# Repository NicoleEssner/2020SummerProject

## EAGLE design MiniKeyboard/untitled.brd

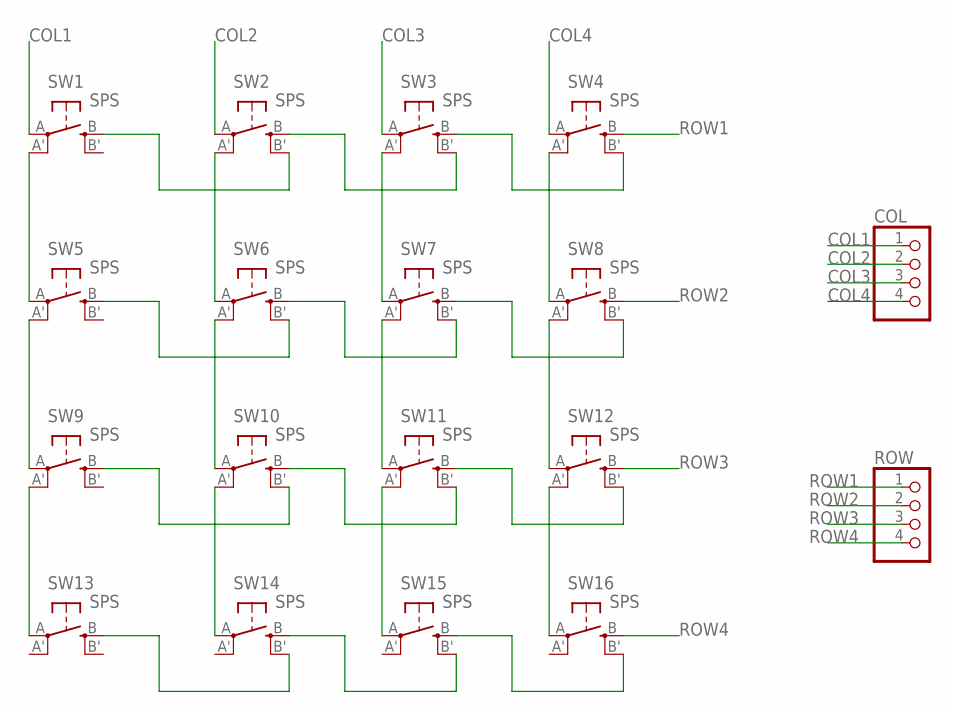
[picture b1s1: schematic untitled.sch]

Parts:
COL: PINHD-1X4; 1X04
ROW: PINHD-1X4; 1X04
SW1, SW2, SW3, SW4, SW5, SW6, SW7, SW8, SW9, SW10, SW11, SW12, SW13, SW14, SW15, SW16: SPS; EVQ-Q2

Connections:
COL1: COL.1, SW1.A
COL2: COL.2, SW2.A
COL3: COL.3, SW3.A
COL4: COL.4, SW4.A
unnamed: SW1.A' (P1), SW5.A
unnamed: SW5.A' (P1), SW9.A
unnamed: SW9.A' (P1), SW13.A
unnamed: SW2.A' (P1), SW6.A
unnamed: SW6.A' (P1), SW10.A
unnamed: SW10.A' (P1), SW14.A
unnamed: SW3.A' (P1), SW7.A
unnamed: SW7.A' (P1), SW11.A
unnamed: SW11.A' (P1), SW15.A
unnamed: SW4.A' (P1), SW8.A
unnamed: SW8.A' (P1), SW12.A
unnamed: SW12.A' (P1), SW16.A
unnamed: SW1.B (S), SW2.B' (S1)
unnamed: SW2.B (S), SW3.B' (S1)
unnamed: SW3.B (S), SW4.B' (S1)
unnamed: SW5.B (S), SW6.B' (S1)
unnamed: SW6.B (S), SW7.B' (S1)
unnamed: SW7.B (S), SW8.B' (S1)
unnamed: SW9.B (S), SW10.B' (S1)
unnamed: SW10.B (S), SW11.B' (S1)
unnamed: SW11.B (S), SW12.B' (S1)
unnamed: SW13.B (S), SW14.B' (S1)
unnamed: SW14.B (S), SW15.B' (S1)
unnamed: SW15.B (S), SW16.B' (S1)
ROW1: ROW.1, SW4.B (S)
ROW2: ROW.2, SW8.B (S)
ROW3: ROW.3, SW12.B (S)
ROW4: ROW.4, SW16.B (S)

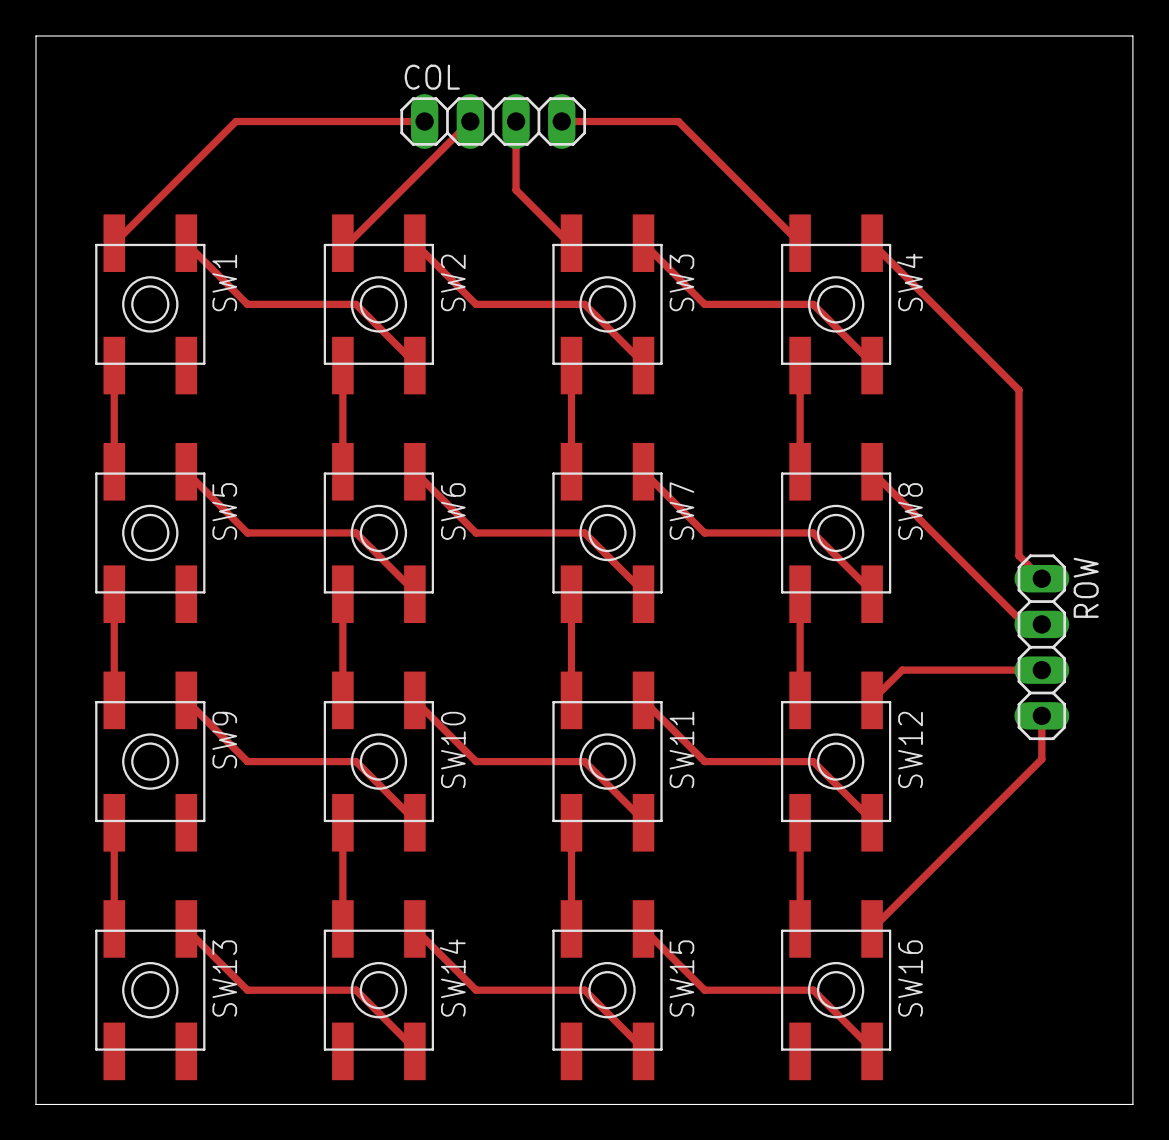
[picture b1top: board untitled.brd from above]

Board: 2 copper layers, 60.9 x 59.4 mm, 18 parts (0 on the bottom side), 32 nets.

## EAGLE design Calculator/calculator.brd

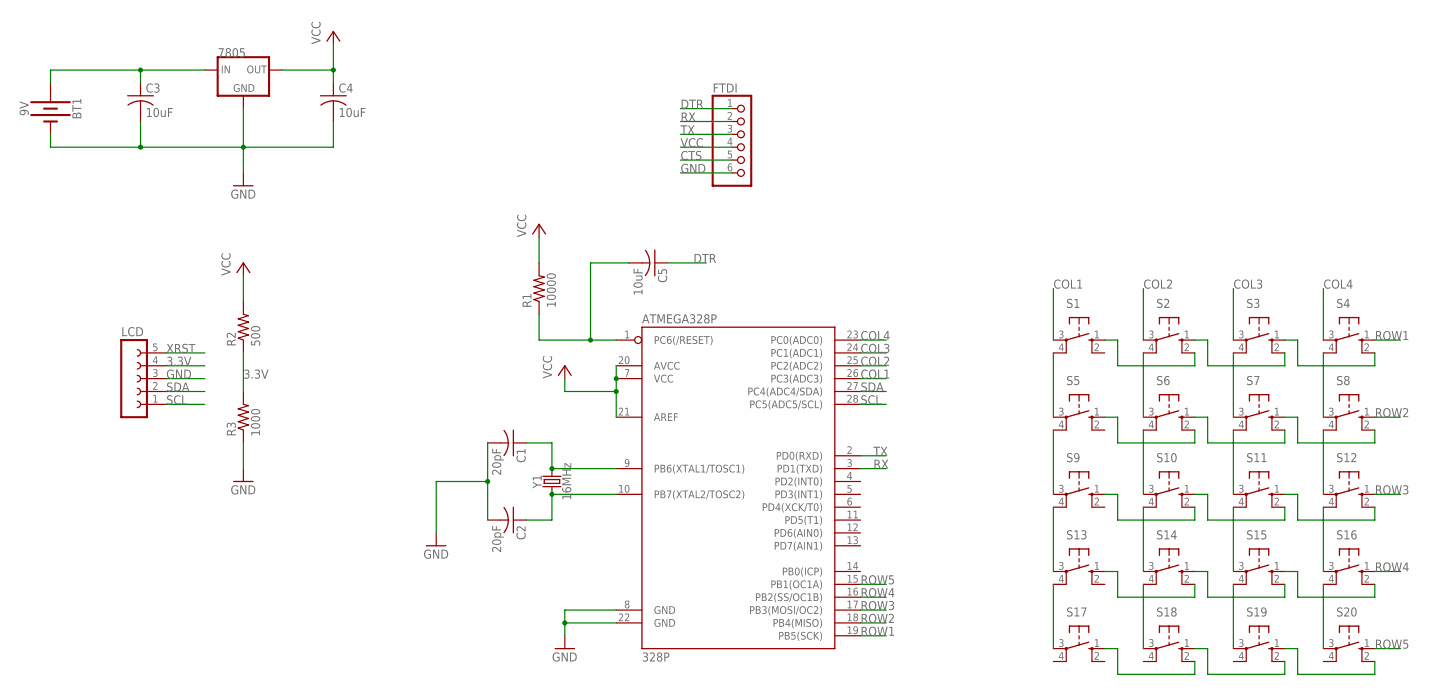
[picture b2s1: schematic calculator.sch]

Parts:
7805: 78XXS
ATMEGA328P: 328P; DIP28
BT1: 9V; BATTCON_9V
C1, C2: 20pF; C025-024X044
C3, C4, C5: 10uF; C025-024X044
FTDI: PINHD-1X6; 1X06
LCD: FE05-1
R1: 10000; 0204/7
R2: 500; 0204/7
R3: 1000; 0204/7
S1, S2, S3, S4, S5, S6, S7, S8, S9, S10, S11, S12, S13, S14, S15, S16, S17, S18, S19, S20: 10-XX; B3F-10XX
Y1: 16MHz; HC49US

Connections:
3.3V: LCD.4, R2.1, R3.2
COL1: ATMEGA328P.26 (PC3(ADC3)), S1.3
COL2: ATMEGA328P.25 (PC2(ADC2)), S2.3
COL3: ATMEGA328P.24 (PC1(ADC1)), S3.3
COL4: ATMEGA328P.23 (PC0(ADC0)), S4.3
CTS: FTDI.5
DTR: C5.1, FTDI.1
GND: 7805.GND, ATMEGA328P.8 (GND), ATMEGA328P.22 (GND), BT1.-, C1.2, C2.2, C3.2, C4.2, FTDI.6, LCD.3, R3.1
unnamed: 7805.IN, BT1.+, C3.1
unnamed: ATMEGA328P.10 (PB7(XTAL2/TOSC2)), C2.1, Y1.1
unnamed: ATMEGA328P.9 (PB6(XTAL1/TOSC1)), C1.1, Y1.2
unnamed: ATMEGA328P.1 (PC6(/RESET)), C5.2, R1.1
unnamed: S1.4 (P1), S5.3
unnamed: S5.4 (P1), S9.3
unnamed: S9.4 (P1), S13.3
unnamed: S13.4 (P1), S17.3
unnamed: S1.1 (S), S2.2 (S1)
unnamed: S2.4 (P1), S6.3
unnamed: S6.4 (P1), S10.3
unnamed: S10.4 (P1), S14.3
unnamed: S14.4 (P1), S18.3
unnamed: S3.1 (S), S4.2 (S1)
unnamed: S3.4 (P1), S7.3
unnamed: S7.4 (P1), S11.3
unnamed: S11.4 (P1), S15.3
unnamed: S15.4 (P1), S19.3
unnamed: S9.1 (S), S10.2 (S1)
unnamed: S4.4 (P1), S8.3
unnamed: S8.4 (P1), S12.3
unnamed: S12.4 (P1), S16.3
unnamed: S16.4 (P1), S20.3
unnamed: S13.1 (S), S14.2 (S1)
unnamed: S17.1 (S), S18.2 (S1)
unnamed: S2.1 (S), S3.2 (S1)
unnamed: S5.1 (S), S6.2 (S1)
unnamed: S6.1 (S), S7.2 (S1)
unnamed: S7.1 (S), S8.2 (S1)
unnamed: S10.1 (S), S11.2 (S1)
unnamed: S11.1 (S), S12.2 (S1)
unnamed: S14.1 (S), S15.2 (S1)
unnamed: S15.1 (S), S16.2 (S1)
unnamed: S18.1 (S), S19.2 (S1)
unnamed: S19.1 (S), S20.2 (S1)
ROW1: ATMEGA328P.19 (PB5(SCK)), S4.1 (S)
ROW2: ATMEGA328P.18 (PB4(MISO)), S8.1 (S)
ROW3: ATMEGA328P.17 (PB3(MOSI/OC2)), S12.1 (S)
ROW4: ATMEGA328P.16 (PB2(SS/OC1B)), S16.1 (S)
ROW5: ATMEGA328P.15 (PB1(OC1A)), S20.1 (S)
RX: ATMEGA328P.3 (PD1(TXD)), FTDI.2
SCL: ATMEGA328P.28 (PC5(ADC5/SCL)), LCD.1
SDA: ATMEGA328P.27 (PC4(ADC4/SDA)), LCD.2
TX: ATMEGA328P.2 (PD0(RXD)), FTDI.3
VCC: 7805.OUT, ATMEGA328P.7 (VCC), ATMEGA328P.20 (AVCC), ATMEGA328P.21 (AREF), C4.1, FTDI.4, R1.2, R2.2
XRST: LCD.5

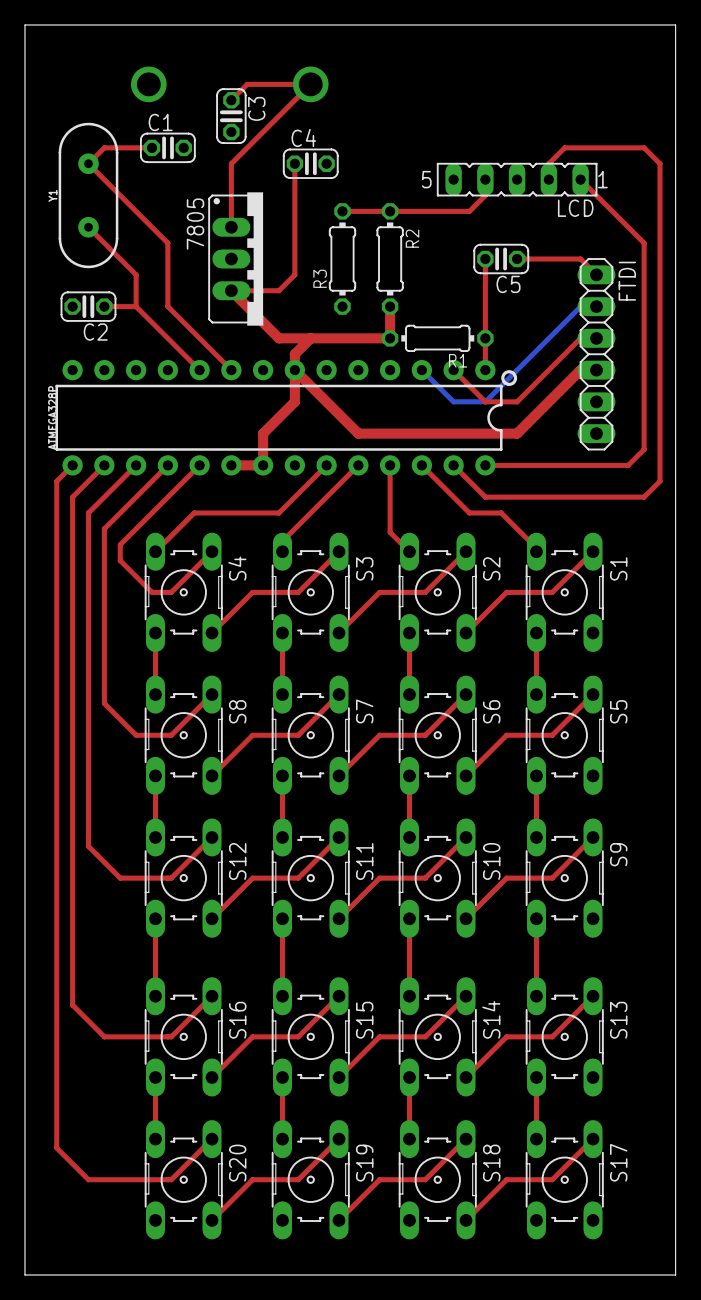
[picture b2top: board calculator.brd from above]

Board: 2 copper layers, 52.0 x 100.0 mm, 34 parts (1 on the bottom side), 52 nets.

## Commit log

2020-08-11 Files for summer 2020 project

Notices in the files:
parts and their libraries:
SparkFun-IC-Microcontroller: Licensing: Creative Commons ShareAlike 4.0 International - https://creativecommons.org/licenses/by-sa/4.0
